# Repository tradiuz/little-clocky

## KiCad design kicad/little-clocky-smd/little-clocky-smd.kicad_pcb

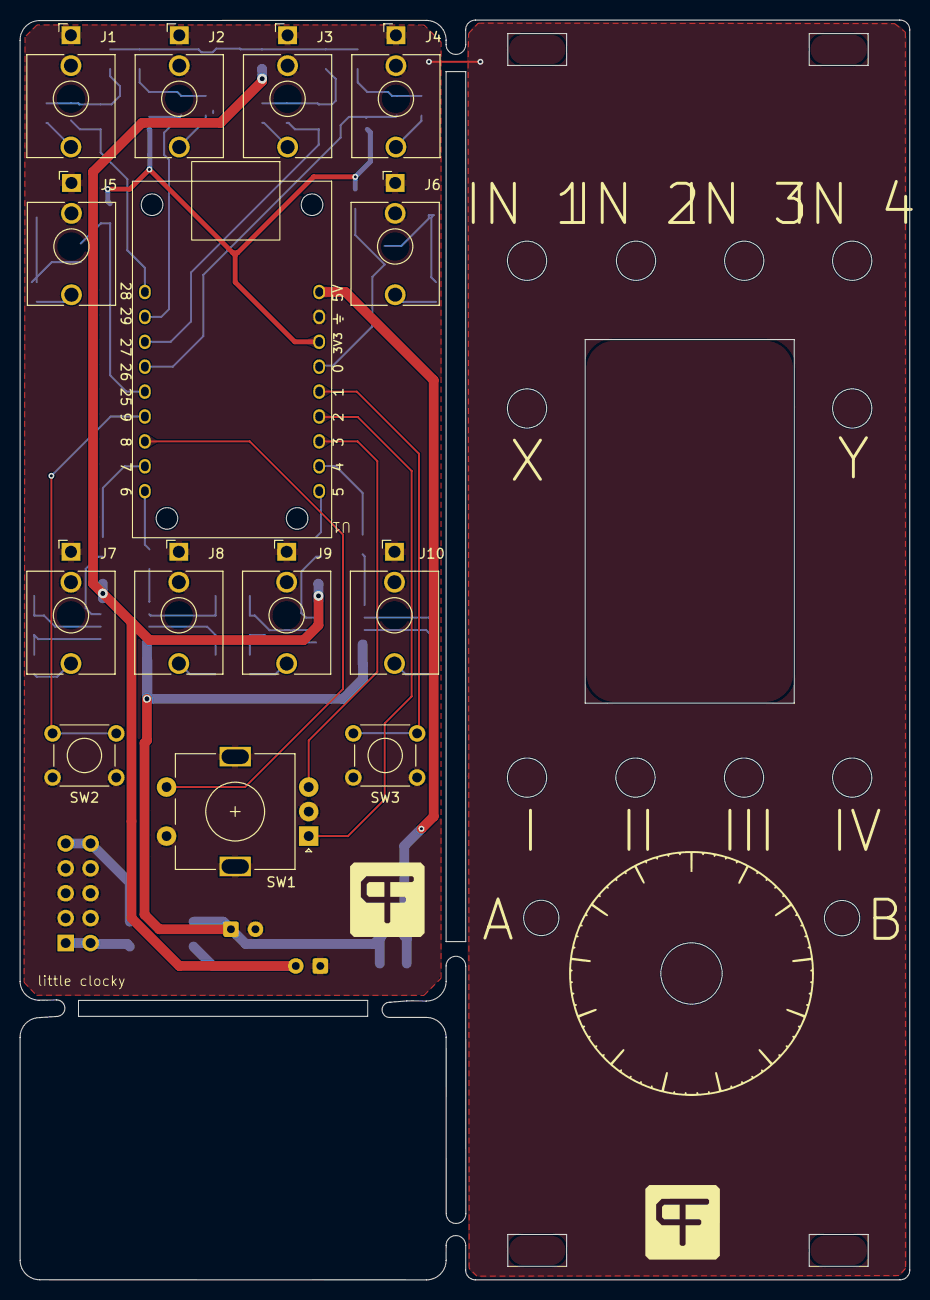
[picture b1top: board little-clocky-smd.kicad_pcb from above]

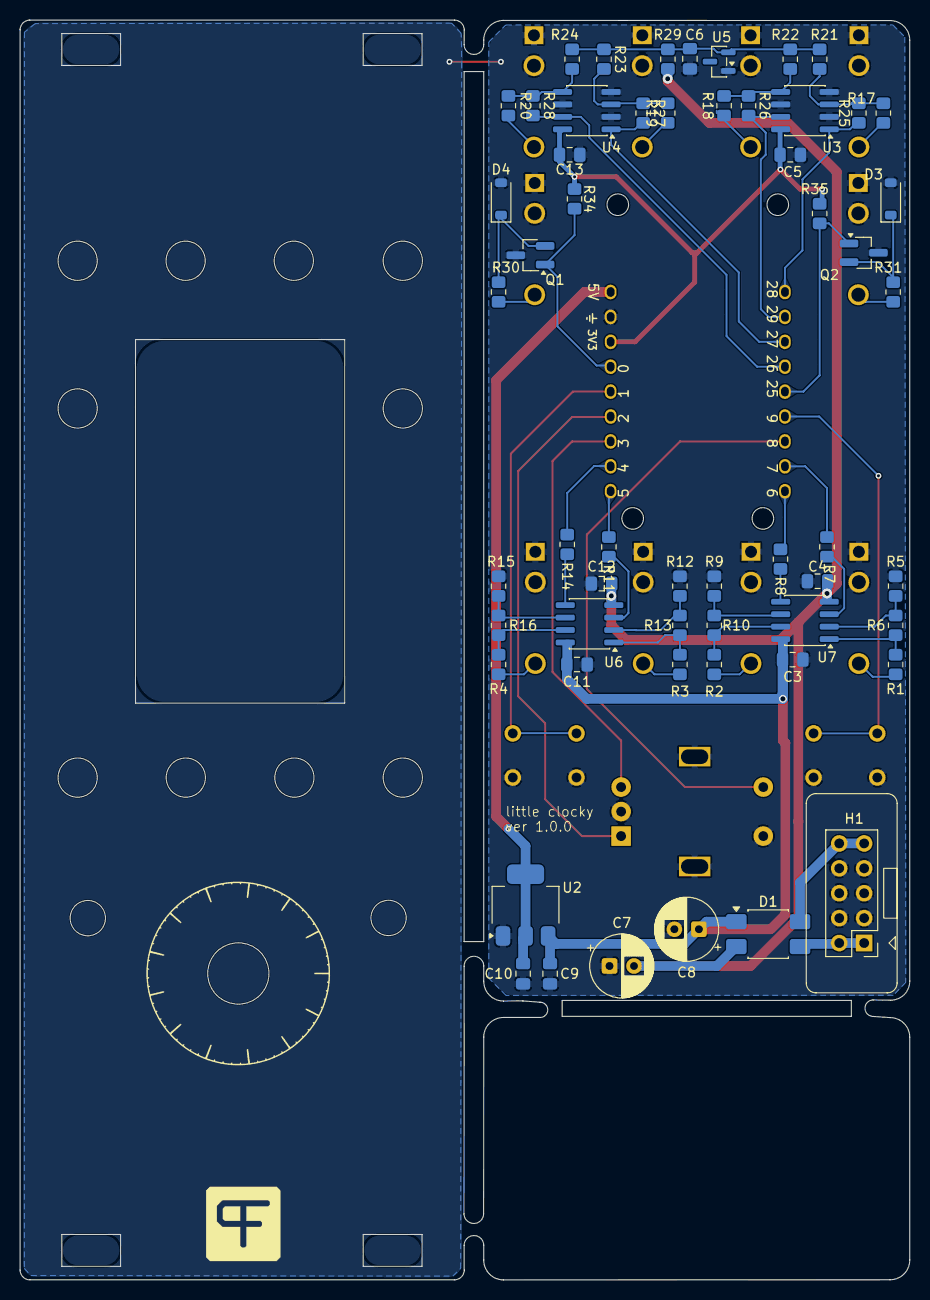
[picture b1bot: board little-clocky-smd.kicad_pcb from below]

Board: 2 copper layers, 90.7 x 128.5 mm, 70 parts (56 on the bottom side), 51 nets.

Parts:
C3, C4, C5, C6, C11, C12, C13: 100nF; C_0805_2012Metric_Pad1.18x1.45mm_HandSolder
C7, C8: 47uF; CP_Radial_D6.3mm_P2.50mm
C9: 10uF; C_0805_2012Metric_Pad1.18x1.45mm_HandSolder
C10: 22uF; C_0805_2012Metric_Pad1.18x1.45mm_HandSolder
D1: MB1S; OnSemi_751EP_SOIC-4_3.9x4.725mm_P2.54mm
D3, D4: 1N4148W; D_SOD-123
H1: Conn_02x05_Odd_Even; PinHeader_2x05_P2.54mm_Vertical
J1, J2, J3, J4, J5, J6, J7, J8, J9, J10: WQP518MA; Jack_3.5mm_Thonkiconn_WQP-PJ398SM_Vertical_CircularHoles
Q1, Q2: NPN; SOT-23_Handsoldering
R1, R2, R3, R4: 1k; R_0805_2012Metric_Pad1.20x1.40mm_HandSolder
R5, R6, R7, R8, R9, R10, R11, R12, R13, R14, R15, R16, R34, R35: 10k; R_0805_2012Metric_Pad1.20x1.40mm_HandSolder
R17, R18, R19, R20, R30, R31: 100k; R_0805_2012Metric_Pad1.20x1.40mm_HandSolder
R21, R22, R23, R24: 200k; R_0805_2012Metric_Pad1.20x1.40mm_HandSolder
R25, R26, R27, R28: 33k; R_0805_2012Metric_Pad1.20x1.40mm_HandSolder
R29: 470; R_0805_2012Metric_Pad1.20x1.40mm_HandSolder
SW1: RotaryEncoder_Switch; RotaryEncoder_Alps_EC11E-Switch_Vertical_H20mm
SW2, SW3: SW_Push; SW_TH_Tactile_Omron_B3F-107x
U1: Waveshare RP2350-LCD-1.47
U2: AZ1117-5.0; SOT-223-3_TabPin2
U3, U4: MCP6002-xSN; SOIC-8_3.9x4.9mm_P1.27mm
U5: LM4040DBZ-10; SOT-23
U6, U7: TL072; SOIC-8_3.9x4.9mm_P1.27mm

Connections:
+3.3V: C5.1, C13.1, R34.2, R35.2, U1.3 (3V3), U3.8 (V+), U4.8 (V+)
+5V: C10.1, U1.1 (5V), U2.2 (VO)
+12V: C3.1, C8.1, C9.1, C11.1, D1.1 (+), U2.3 (VI), U6.8 (V+), U7.8 (V+)
-12V: C4.1, C7.2, C12.1, D1.2 (-), R29.1, U6.4 (V-), U7.4 (V-)
ADC0: R25.2, U1.18 (GPIO_28), U3.1
ADC1: R26.2, U1.17 (ADC3), U3.7
ADC2: R27.2, U1.16 (ADC1), U4.1
ADC3: R28.2, U1.15 (ADC0), U4.7
AREF_-10V: C6.2, R21.1, R22.1, R23.1, R24.1, R29.2, U5.2 (A)
BTN1: SW2.2, U1.13 (GPIO_09)
BTN2: SW3.2, U1.5 (GPIO_01)
ENCA: SW1.A, U1.6 (GPIO_02)
ENCB: SW1.B, U1.7 (GPIO_03)
ENCS: SW1.S1, U1.12 (GPIO_08)
GATE_OUT1: R7.1, U1.11 (GPIO_07)
GATE_OUT2: R8.1, U1.10 (GPIO_06)
GATE_OUT3: R11.1, U1.9 (GPIO_05)
GATE_OUT4: R14.1, U1.8 (GPIO_04)
GND: C3.2, C4.2, C5.2, C6.1, C7.1, C8.2, C9.2, C10.2, C11.2, C12.2, C13.2, D3.2 (A), D4.2 (A), H1.3, H1.4, H1.5, H1.6, H1.7, H1.8, J1.S, J1.TN, J2.S, J2.TN, J3.S, J3.TN, J4.S, J4.TN, J5.S, J5.TN, J6.S, J6.TN, J7.S, J7.TN, J8.S, J8.TN, J9.S, J9.TN, J10.S, J10.TN, Q1.3 (E), Q2.3 (E), R5.1, R9.1, R12.1, R15.1, SW1.C, SW1.MP, SW1.S2, SW2.1, SW3.1, U1.2 (GND), U2.1 (GND), U3.2 (-), U3.4 (V-), U3.6 (-), U4.2 (-), U4.4 (V-), U4.6 (-), U5.1 (K)
unnamed: D3.1 (K), Q2.2 (B), R31.2
unnamed: D4.1 (K), Q1.2 (B), R30.2
unnamed: D1.3, H1.1, H1.2
unnamed: D1.4, H1.9, H1.10
unnamed: J1.T, R17.1
unnamed: J2.T, R18.1
unnamed: J3.T, R19.1
unnamed: J4.T, R20.1
unnamed: J5.T, R31.1
unnamed: J6.T, R30.1
unnamed: J7.T, R1.2
unnamed: J8.T, R2.2
unnamed: J9.T, R3.2
unnamed: J10.T, R4.2
unnamed: R1.1, R6.2, U7.1
unnamed: R2.1, R10.2, U7.7
unnamed: R3.1, R13.2, U6.1
unnamed: R4.1, R16.2, U6.7
unnamed: R17.2, R21.2, R25.1, U3.3 (+)
unnamed: R18.2, R22.2, R26.1, U3.5 (+)
unnamed: R19.2, R23.2, R27.1, U4.3 (+)
unnamed: R20.2, R24.2, R28.1, U4.5 (+)
unnamed: R11.2, U6.3 (+)
unnamed: R12.2, R13.1, U6.2 (-)
unnamed: R14.2, U6.5 (+)
unnamed: R15.2, R16.1, U6.6 (-)
unnamed: R7.2, U7.3 (+)
unnamed: R5.2, R6.1, U7.2 (-)
unnamed: R8.2, U7.5 (+)
unnamed: R9.2, R10.1, U7.6 (-)
TRIG1: Q2.1 (C), R35.1, U1.14 (UART0_RX)
TRIG2: Q1.1 (C), R34.1, U1.4 (GPIO_00)

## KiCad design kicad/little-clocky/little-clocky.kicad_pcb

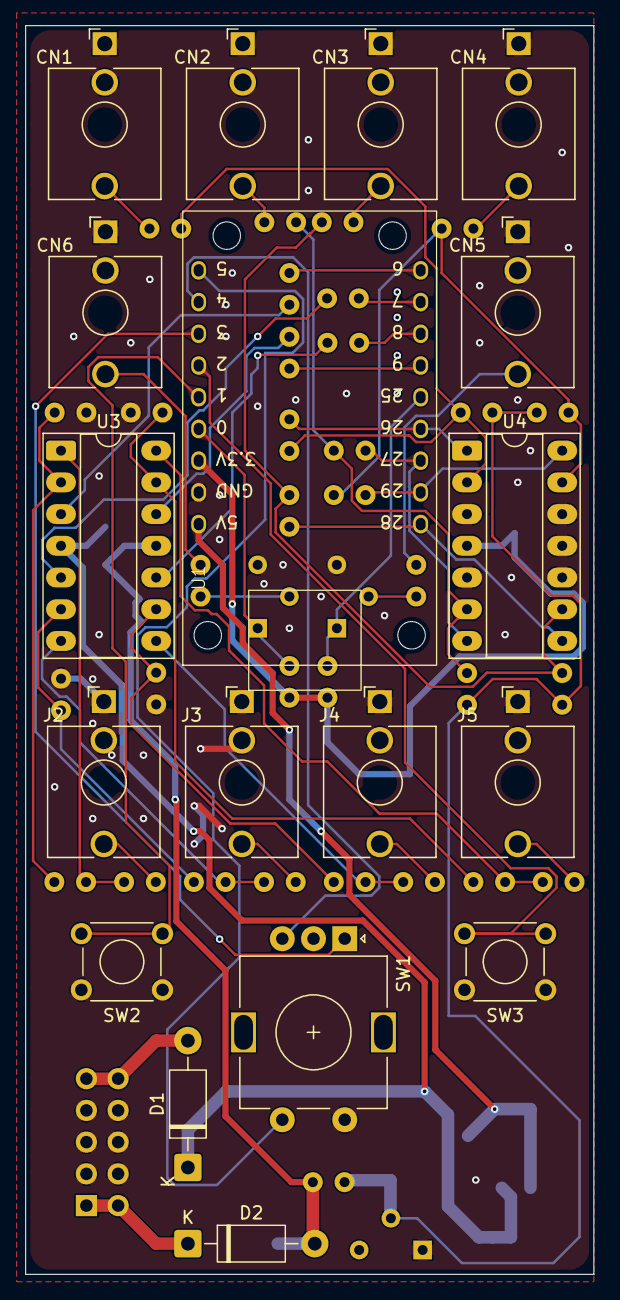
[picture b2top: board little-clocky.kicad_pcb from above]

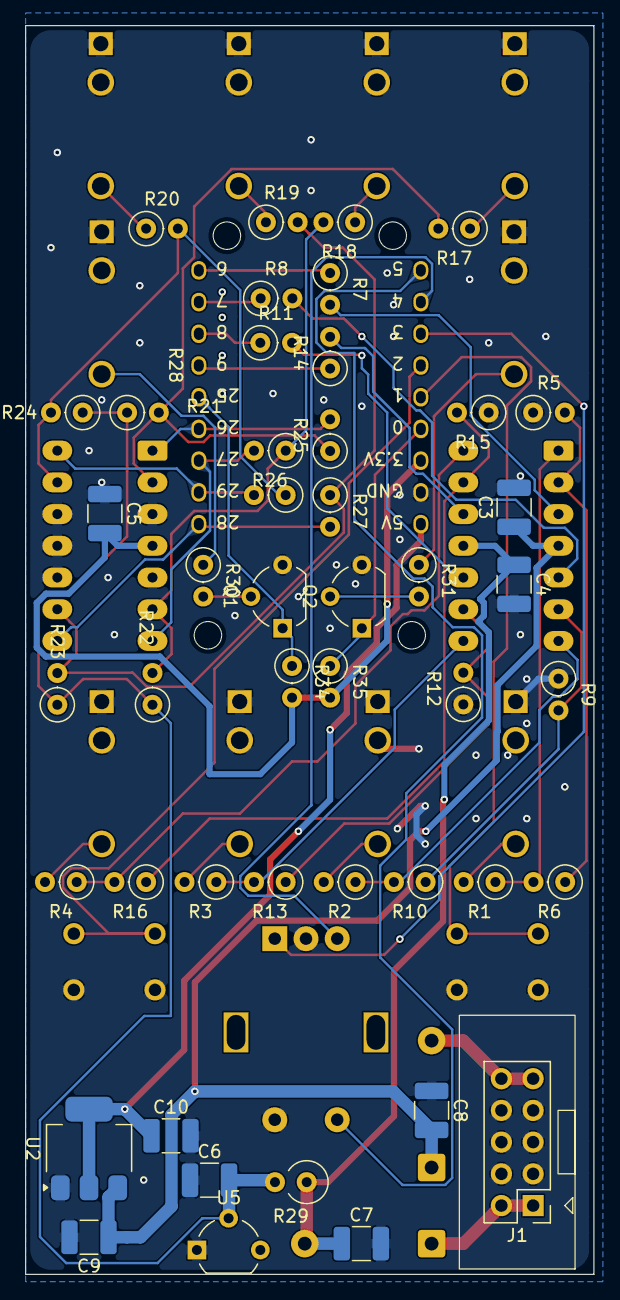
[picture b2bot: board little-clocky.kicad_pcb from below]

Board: 2 copper layers, 45.5 x 100.0 mm, 64 parts (46 on the bottom side), 51 nets.

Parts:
C3, C4, C5, C6: 100nF; C_1210_3225Metric_Pad1.33x2.70mm_HandSolder
C7, C8: 47uF; C_1210_3225Metric_Pad1.33x2.70mm_HandSolder
C9: 10uF; C_1210_3225Metric_Pad1.33x2.70mm_HandSolder
C10: 22uF; C_1210_3225Metric_Pad1.33x2.70mm_HandSolder
CN1, CN2, CN3, CN4, CN5, CN6: WQP518MA; Jack_3.5mm_QingPu_WQP-PJ398SM_Vertical_CircularHoles
D1, D2: 1N4001; D_DO-41_SOD81_P10.16mm_Horizontal
J1: Conn_02x05_Odd_Even; PinHeader_2x05_P2.54mm_Vertical
J2, J3, J4, J5: WQP518MA; Jack_3.5mm_QingPu_WQP-PJ398SM_Vertical_CircularHoles
Q1, Q2: NPN; TO-92_Wide
R1, R2, R3, R4: 1k; R_Axial_DIN0207_L6.3mm_D2.5mm_P2.54mm_Vertical
R5, R6, R7, R8, R9, R10, R11, R12, R13, R14, R15, R16: 10k; R_Axial_DIN0207_L6.3mm_D2.5mm_P2.54mm_Vertical
R17, R18, R19, R20, R30, R31, R34, R35: 100k; R_Axial_DIN0207_L6.3mm_D2.5mm_P2.54mm_Vertical
R21, R22, R23, R24: 200k; R_Axial_DIN0207_L6.3mm_D2.5mm_P2.54mm_Vertical
R25, R26, R27, R28: 33k; R_Axial_DIN0207_L6.3mm_D2.5mm_P2.54mm_Vertical
R29: 470; R_Axial_DIN0309_L9.0mm_D3.2mm_P2.54mm_Vertical
SW1: RotaryEncoder_Switch; RotaryEncoder_Alps_EC11E-Switch_Vertical_H20mm
SW2, SW3: SW_Push; SW_TH_Tactile_Omron_B3F-107x
U1: Waveshare RP2350-LCD-1.47
U2: AZ1117-5.0; SOT-223-3_TabPin2
U3: TL074; DIP-14_W7.62mm_Socket_LongPads
U4: MCP6004; DIP-14_W7.62mm_Socket_LongPads
U5: LM4040DBZ-10; TO-92_Wide

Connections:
+3.3V: C5.2, R34.2, R35.2, U1.3 (3V3), U4.4 (V+)
+5V: C10.1, U1.1 (5V), U2.2 (VO)
+12V: C3.1, C8.2, C9.1, D1.1 (K), U2.3 (VI), U3.4 (V+)
-12V: C4.1, C7.1, D2.2 (A), R29.1, U3.11 (V-)
ADC0: R25.2, U1.15 (ADC0), U4.1
ADC1: R26.2, U1.16 (ADC1), U4.7
ADC2: R27.2, U1.18 (GPIO_28), U4.8
ADC3: R28.2, U1.17 (ADC3), U4.14
AREF_-10V: C6.2, R21.1, R22.1, R23.1, R24.1, R29.2, U5.2 (A)
BTN1: SW2.2, U1.5 (GPIO_01)
BTN2: SW3.2, U1.6 (GPIO_02)
ENCA: SW1.A, U1.7 (GPIO_03)
ENCB: SW1.B, U1.8 (GPIO_04)
ENCS: SW1.S1, U1.9 (GPIO_05)
GATE_OUT1: R7.1, U1.10 (GPIO_06)
GATE_OUT2: R8.1, U1.11 (GPIO_07)
GATE_OUT3: R11.1, U1.12 (GPIO_08)
GATE_OUT4: R14.1, U1.13 (GPIO_09)
GND: C3.2, C4.2, C5.1, C6.1, C7.2, C8.1, C9.2, C10.2, CN1.S, CN1.TN, CN2.S, CN2.TN, CN3.S, CN3.TN, CN4.S, CN4.TN, CN5.S, CN5.TN, CN6.S, CN6.TN, J1.3, J1.4, J1.5, J1.6, J1.7, J1.8, J2.S, J2.TN, J3.S, J3.TN, J4.S, J4.TN, J5.S, J5.TN, Q1.3 (E), Q2.3 (E), R5.1, R9.1, R12.1, R15.1, SW1.C, SW1.S2, SW2.1, SW3.1, U1.2 (GND), U2.1 (GND), U4.3 (+), U4.5 (+), U4.10 (+), U4.11 (V-), U4.12 (+), U5.1 (K)
unnamed: CN1.T, R17.1
unnamed: CN2.T, R18.1
unnamed: CN3.T, R19.1
unnamed: CN4.T, R20.1
unnamed: CN5.T, R30.1
unnamed: CN6.T, R31.1
unnamed: D1.2 (A), J1.9, J1.10
unnamed: D2.1 (K), J1.1, J1.2
unnamed: J2.T, R1.2
unnamed: J3.T, R2.2
unnamed: J4.T, R3.2
unnamed: J5.T, R4.2
unnamed: Q1.2 (B), R30.2
unnamed: Q2.2 (B), R31.2
unnamed: R1.1, R6.2, U3.1
unnamed: R2.1, R10.2, U3.7
unnamed: R3.1, R13.2, U3.8
unnamed: R4.1, R16.2, U3.14
unnamed: R7.2, U3.3 (+)
unnamed: R5.2, R6.1, U3.2 (-)
unnamed: R8.2, U3.5 (+)
unnamed: R9.2, R10.1, U3.6 (-)
unnamed: R11.2, U3.10 (+)
unnamed: R12.2, R13.1, U3.9 (-)
unnamed: R14.2, U3.12 (+)
unnamed: R15.2, R16.1, U3.13 (-)
unnamed: R17.2, R21.2, R25.1, U4.2 (-)
unnamed: R18.2, R22.2, R26.1, U4.6 (-)
unnamed: R19.2, R23.2, R27.1, U4.9 (-)
unnamed: R20.2, R24.2, R28.1, U4.13 (-)
TRIG1: Q2.1 (C), R35.1, U1.4 (GPIO_00)
TRIG2: Q1.1 (C), R34.1, U1.14 (UART0_RX)

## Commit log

2026-03-25 beat magic
2026-03-28 like 5 different PCB refreshes
